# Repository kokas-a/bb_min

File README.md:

# bb_min

# Prepare u-boot:

export ARCH=arm

export CROSS_COMPILE=arm-none-eabi-

cp config_bbb .config

# Prepare SD-Card:

export DISK=/dev/sdb

dd if=/dev/zero of=${DISK} bs=1M count=10

dd if=./MLO of=${DISK} count=1 seek=1 bs=128k

dd if=./u-boot.img of=${DISK} count=2 seek=1 bs=384k

setenv serverip 10.10.0.1

setenv ipaddr 10.10.0.12

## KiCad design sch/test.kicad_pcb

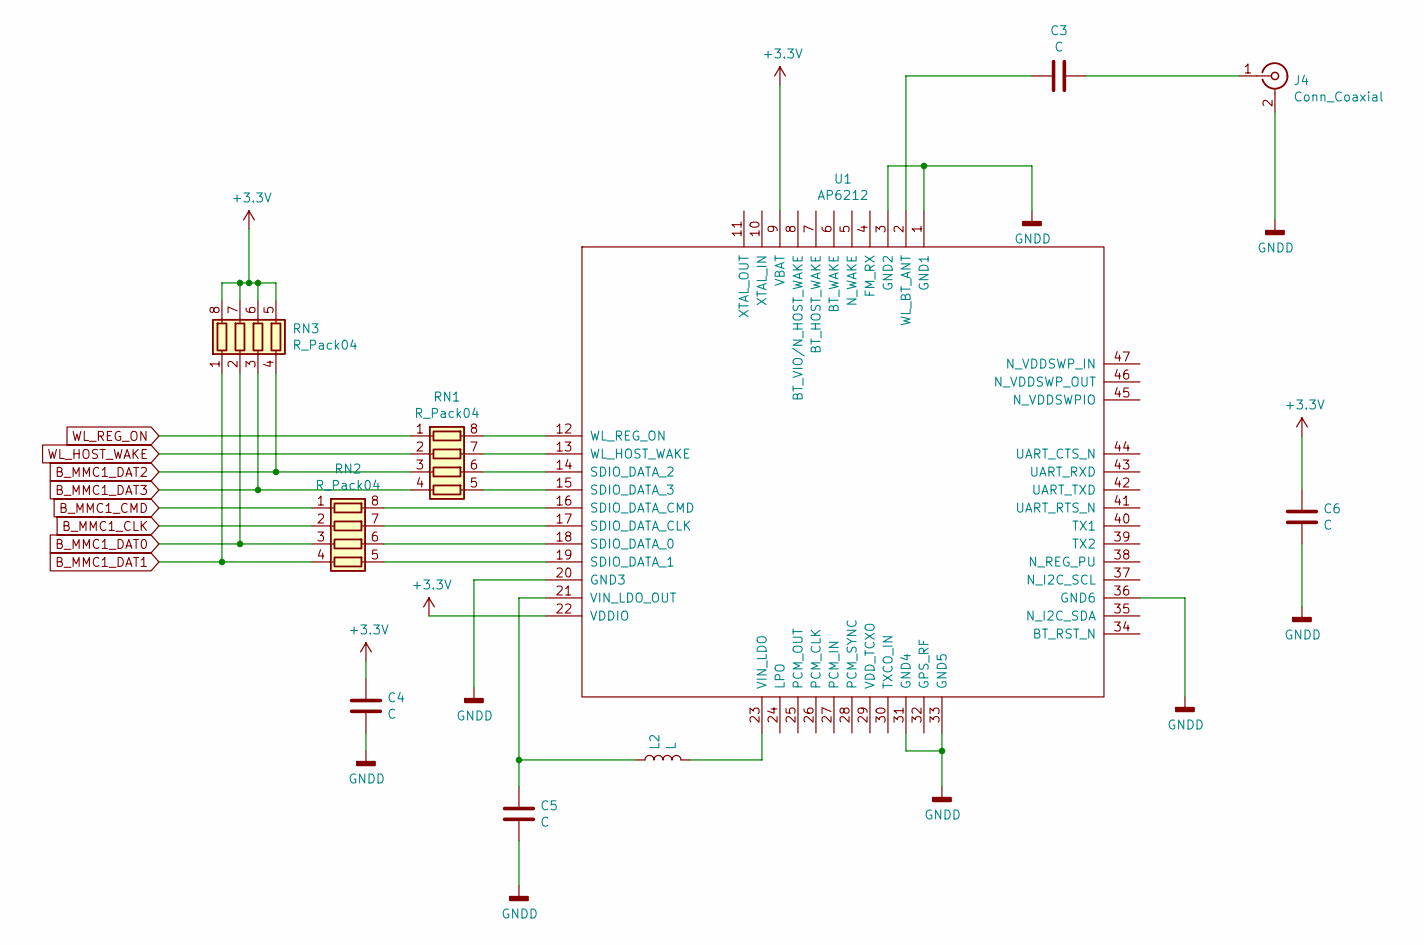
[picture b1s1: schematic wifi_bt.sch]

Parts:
C3: C; C_0603_1608Metric
C4, C5, C6: C; C_0805_2012Metric
J4: Conn_Coaxial; U.FL_Molex_MCRF_73412-0110_Vertical
L2: L; L_1206_3216Metric
RN1, RN2, RN3: R_Pack04; R_Array_Convex_4x0603
U1: AP6212

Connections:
+3V3: C4.1, C6.1, RN3.5 (R4.2), RN3.6 (R3.2), RN3.7 (R2.2), RN3.8 (R1.2), U1.9 (VBAT), U1.22 (VDDIO)
B_MMC1_CLK: RN2.2 (R2.1); also elsewhere on the board
B_MMC1_CMD: RN2.1 (R1.1)
B_MMC1_DAT0: RN2.3 (R3.1), RN3.2 (R2.1); also elsewhere on the board
B_MMC1_DAT1: RN2.4 (R4.1), RN3.1 (R1.1); also elsewhere on the board
B_MMC1_DAT2: RN1.3 (R3.1), RN3.4 (R4.1); also elsewhere on the board
B_MMC1_DAT3: RN1.4 (R4.1), RN3.3 (R3.1); also elsewhere on the board
GNDD: C4.2, C5.2, C6.2, J4.2 (Ext), U1.1 (GND1), U1.3 (GND2), U1.20 (GND3), U1.31 (GND4), U1.33 (GND5), U1.36 (GND6); also elsewhere on the board
unnamed: C3.1, J4.1 (In)
unnamed: C3.2, U1.2 (WL_BT_ANT)
unnamed: C5.1, L2.1, U1.21 (VIN_LDO_OUT)
unnamed: L2.2, U1.23 (VIN_LDO)
unnamed: RN1.5 (R4.2), U1.15 (SDIO_DATA_3)
unnamed: RN1.6 (R3.2), U1.14 (SDIO_DATA_2)
unnamed: RN1.7 (R2.2), U1.13 (WL_HOST_WAKE)
unnamed: RN1.8 (R1.2), U1.12 (WL_REG_ON)
unnamed: RN2.5 (R4.2), U1.19 (SDIO_DATA_1)
unnamed: RN2.6 (R3.2), U1.18 (SDIO_DATA_0)
unnamed: RN2.7 (R2.2), U1.17 (SDIO_DATA_CLK)
unnamed: RN2.8 (R1.2), U1.16 (SDIO_DATA_CMD)
WL_HOST_WAKE: RN1.2 (R2.1)
WL_REG_ON: RN1.1 (R1.1)

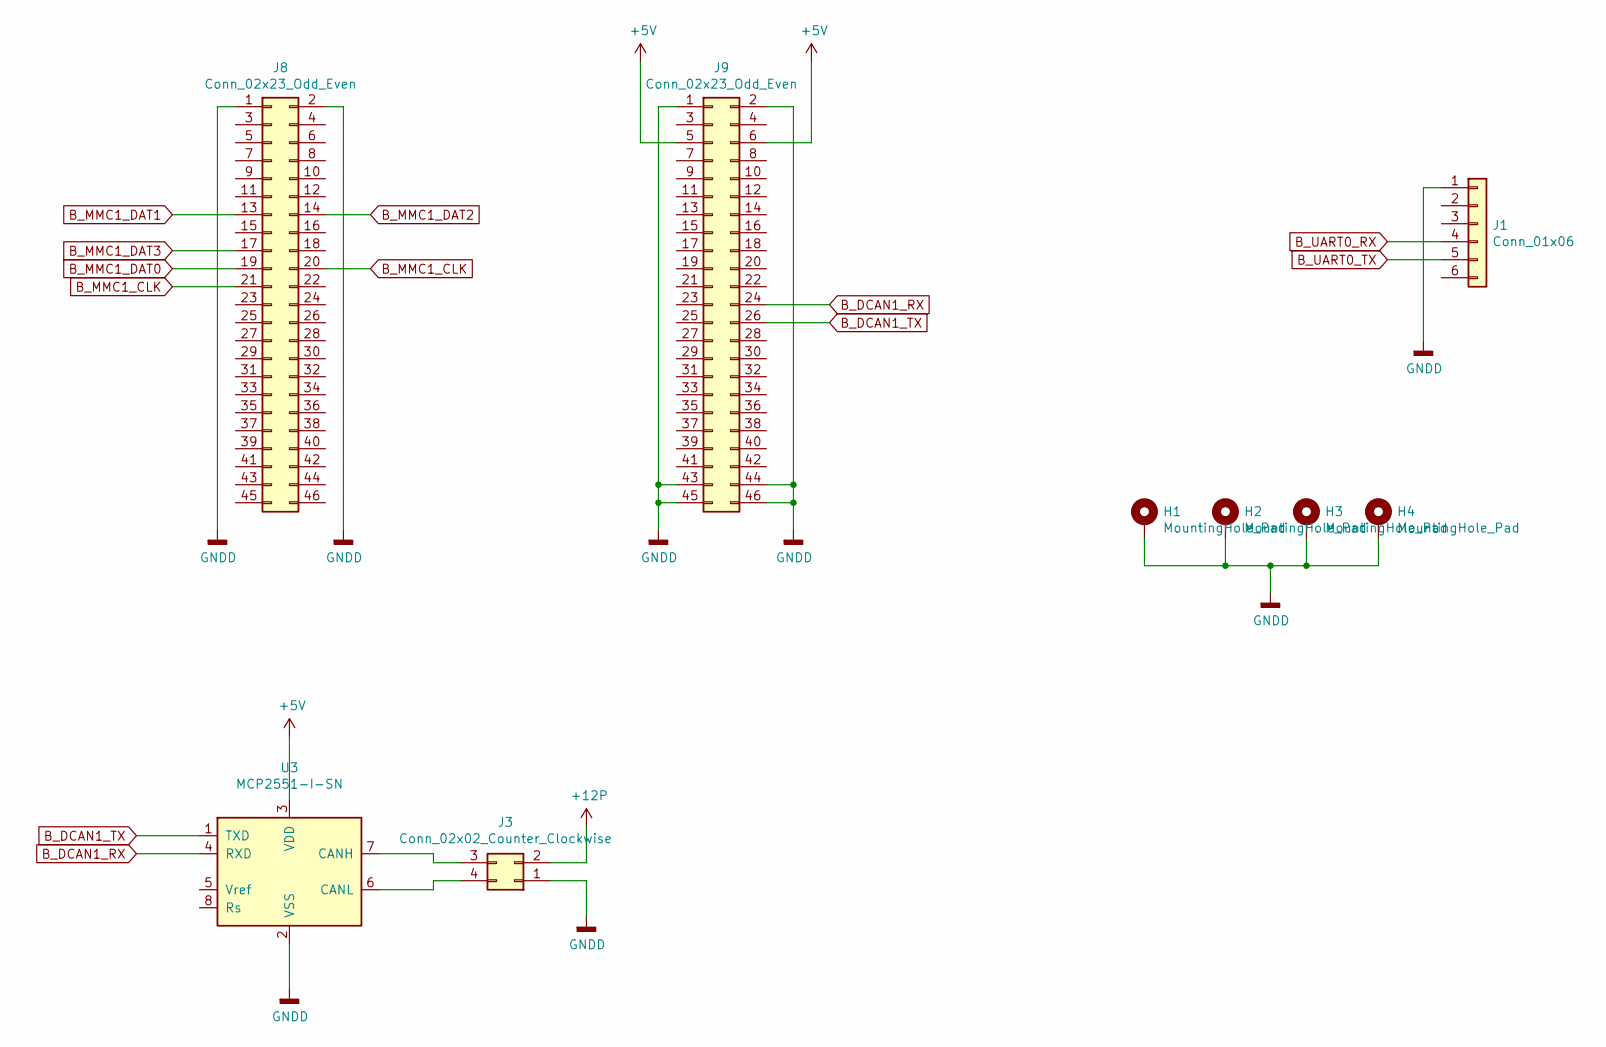
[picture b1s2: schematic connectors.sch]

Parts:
H1, H2, H3, H4: MountingHole_Pad; MountingHole_3.2mm_M3_ISO14580_Pad
J1: Conn_01x06; PinHeader_1x06_P2.54mm_Vertical
J3: Conn_02x02_Counter_Clockwise; PinHeader_1x04_P2.54mm_Horizontal
J8, J9: Conn_02x23_Odd_Even; PinHeader_2x23_P2.54mm_Vertical
U3: MCP2551-I-SN; SOIC-8_3.9x4.9mm_P1.27mm

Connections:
+5V: J9.5, J9.6, U3.3 (VDD); also elsewhere on the board
+12P: J3.2; also elsewhere on the board
B_DCAN1_RX: J9.24, U3.4 (RXD)
B_DCAN1_TX: J9.26, U3.1 (TXD)
B_MMC1_CLK: J8.20, J8.21; also elsewhere on the board
B_MMC1_DAT0: J8.19; also elsewhere on the board
B_MMC1_DAT1: J8.13; also elsewhere on the board
B_MMC1_DAT2: J8.14; also elsewhere on the board
B_MMC1_DAT3: J8.17; also elsewhere on the board
B_UART0_RX: J1.4; also elsewhere on the board
B_UART0_TX: J1.5; also elsewhere on the board
GNDD: H1.1, H2.1, H3.1, H4.1, J1.1, J3.1, J8.1, J8.2, J9.1, J9.2, J9.43, J9.44, J9.45, J9.46, U3.2 (VSS); also elsewhere on the board
unnamed: J3.3, U3.7 (CANH)
unnamed: J3.4, U3.6 (CANL)

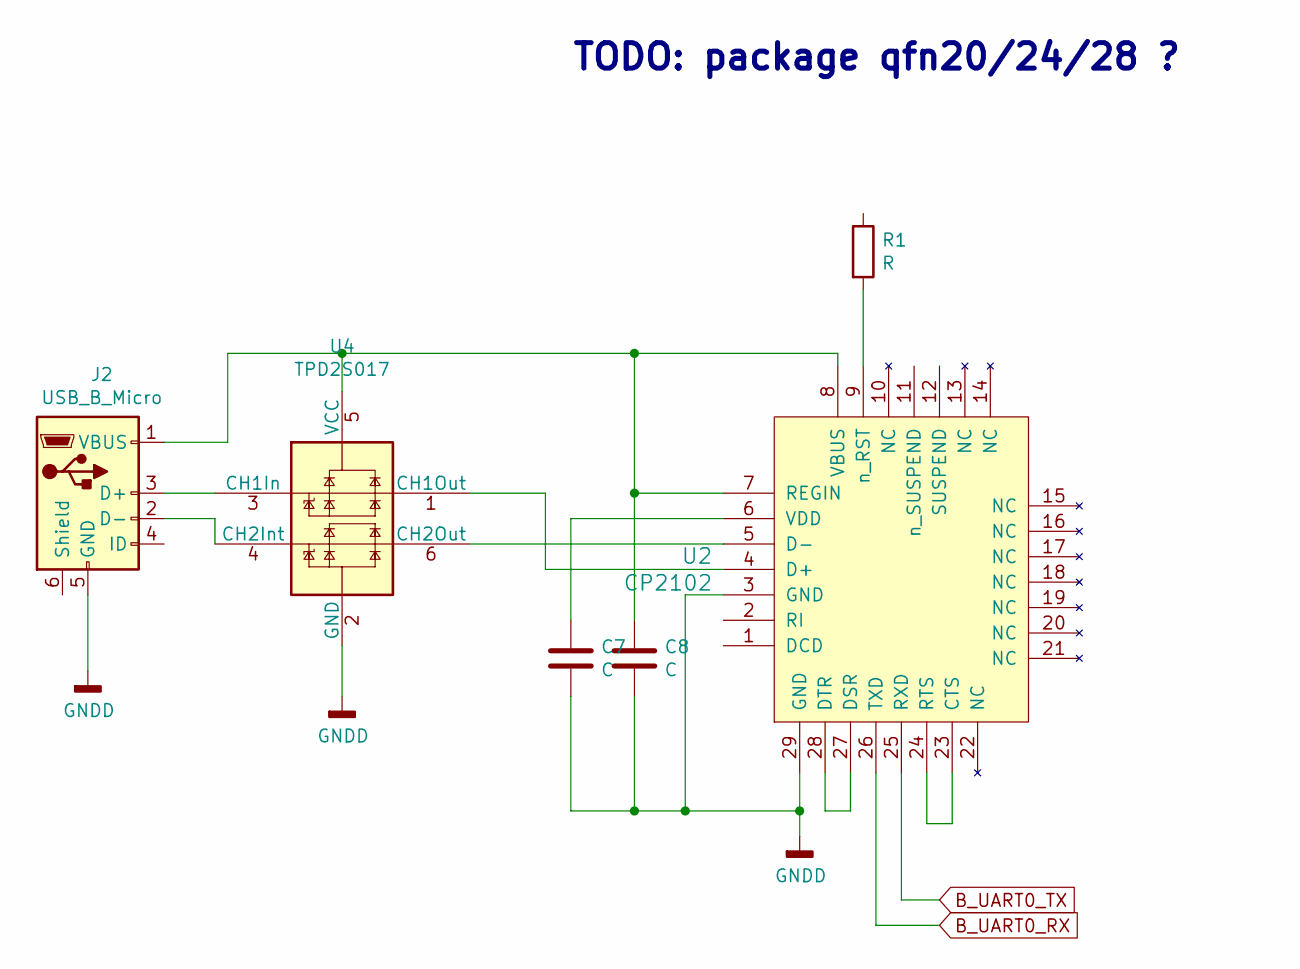
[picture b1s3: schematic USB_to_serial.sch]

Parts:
C7, C8: C; C_0805_2012Metric
J2: USB_B_Micro; USB_Micro-B_Molex_47346-0001
R1: R; R_0603_1608Metric_Pad1.05x0.95mm_HandSolder
U2: CP2102; QFN-28-1EP_5x5mm_P0.5mm_EP3.35x3.35mm
U4: TPD2S017; SOT-23-6

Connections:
B_UART0_RX: U2.26 (TXD); also elsewhere on the board
B_UART0_TX: U2.25 (RXD); also elsewhere on the board
GNDD: C7.2, C8.1, J2.5 (GND), U2.3 (GND), U2.29 (GND), U4.2 (GND); also elsewhere on the board
unnamed: C7.1, U2.6 (VDD)
unnamed: C8.2, J2.1 (VBUS), U2.7 (REGIN), U2.8 (VBUS), U4.5 (VCC)
unnamed: J2.2 (D-), U4.4 (CH2Int)
unnamed: J2.3 (D+), U4.3 (CH1In)
unnamed: R1.2, U2.9 (n_RST)
unnamed: U2.4 (D+), U4.1 (CH1Out)
unnamed: U2.5 (D-), U4.6 (CH2Out)
unnamed: U2.23 (CTS), U2.24 (RTS)
unnamed: U2.27 (DSR), U2.28 (DTR)

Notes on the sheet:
TODO: package qfn20/24/28 ?

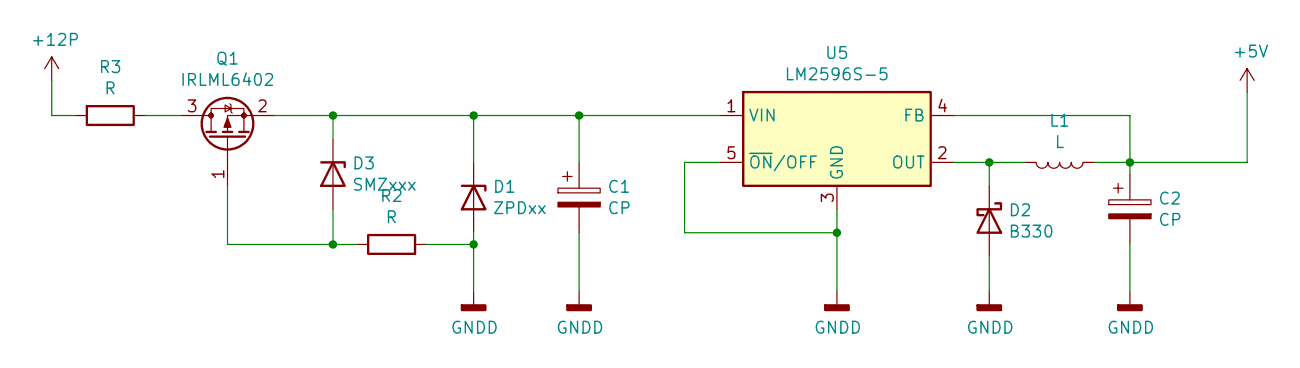
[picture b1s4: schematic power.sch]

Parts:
C1, C2: CP; CP_EIA-6032-28_Kemet-C_Pad2.25x2.35mm_HandSolder
D1: ZPDxx; D_DO-35_SOD27_P7.62mm_Horizontal
D2: B330; D_SMC
D3: SMZxxx; D_MELF
L1: L; L_Bourns_SRR1260
Q1: IRLML6402; SOT-23
R2: R; R_0805_2012Metric_Pad1.15x1.40mm_HandSolder
R3: R; R_1206_3216Metric_Pad1.42x1.75mm_HandSolder
U5: LM2596S-5; TO-263-5_TabPin3

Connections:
+5V: C2.1, L1.1, U5.4 (FB); also elsewhere on the board
+12P: R3.2; also elsewhere on the board
GNDD: C1.2, C2.2, D1.2 (A), D2.2 (A), R2.2, U5.3 (GND), U5.5 (~ON~/OFF); also elsewhere on the board
unnamed: C1.1, D1.1 (K), D3.1 (K), Q1.2 (S), U5.1 (VIN)
unnamed: D2.1 (K), L1.2, U5.2 (OUT)
unnamed: D3.2 (A), Q1.1 (G), R2.1
unnamed: Q1.3 (D), R3.1

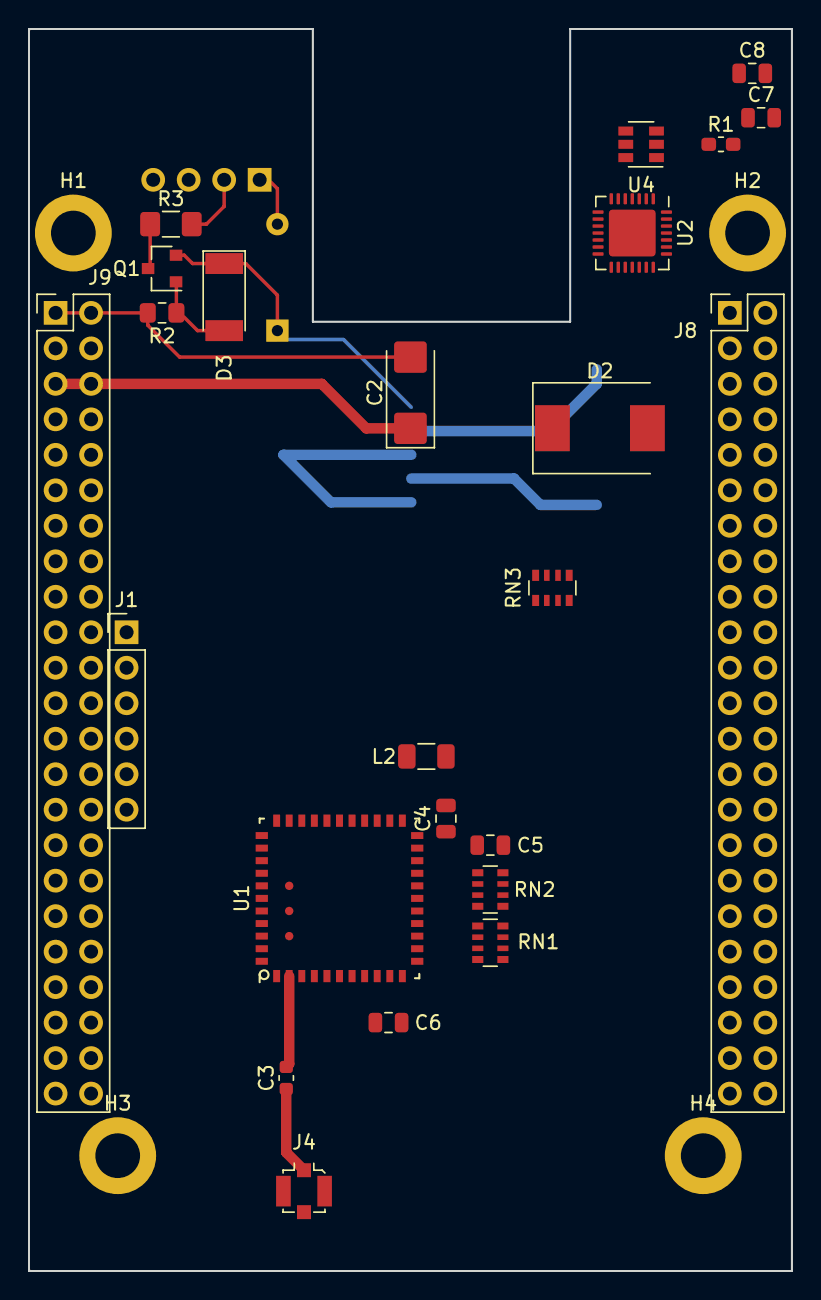
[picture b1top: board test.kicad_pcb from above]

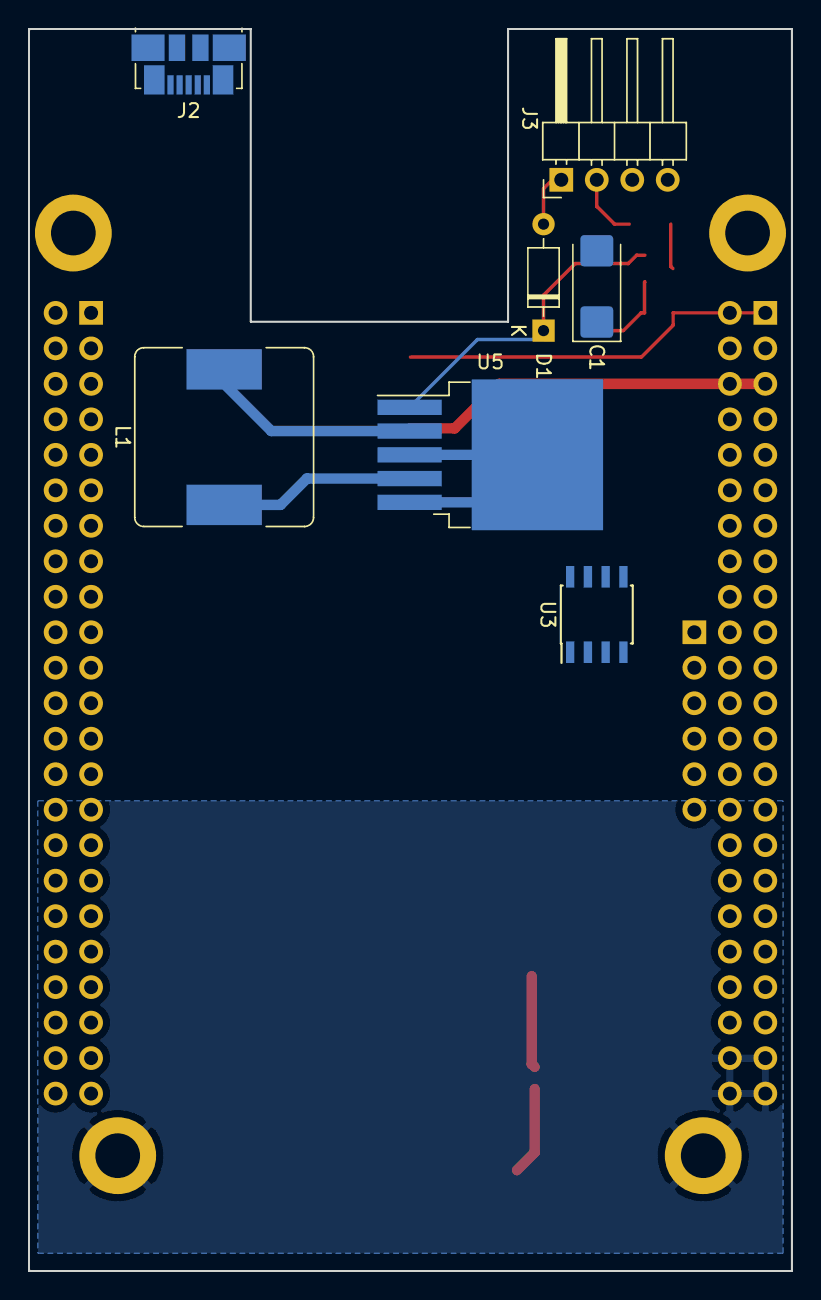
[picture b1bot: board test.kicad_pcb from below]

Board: 4 copper layers, 54.6 x 88.9 mm, 35 parts (7 on the bottom side), 40 nets.

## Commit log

2020-02-13 Add bb-min configs
2020-02-18 fixes
2020-02-20 Add wifi stub
2020-06-02 Add BB cap schemetic
2020-08-31 add u-boot sources
2021-02-11 replace u-boot with new one; decrease bb cpu frequency to 600mhz
2023-04-15 fix lexer fault
2023-04-15 add gitignore
2023-04-15 Fix Nand pinmux
